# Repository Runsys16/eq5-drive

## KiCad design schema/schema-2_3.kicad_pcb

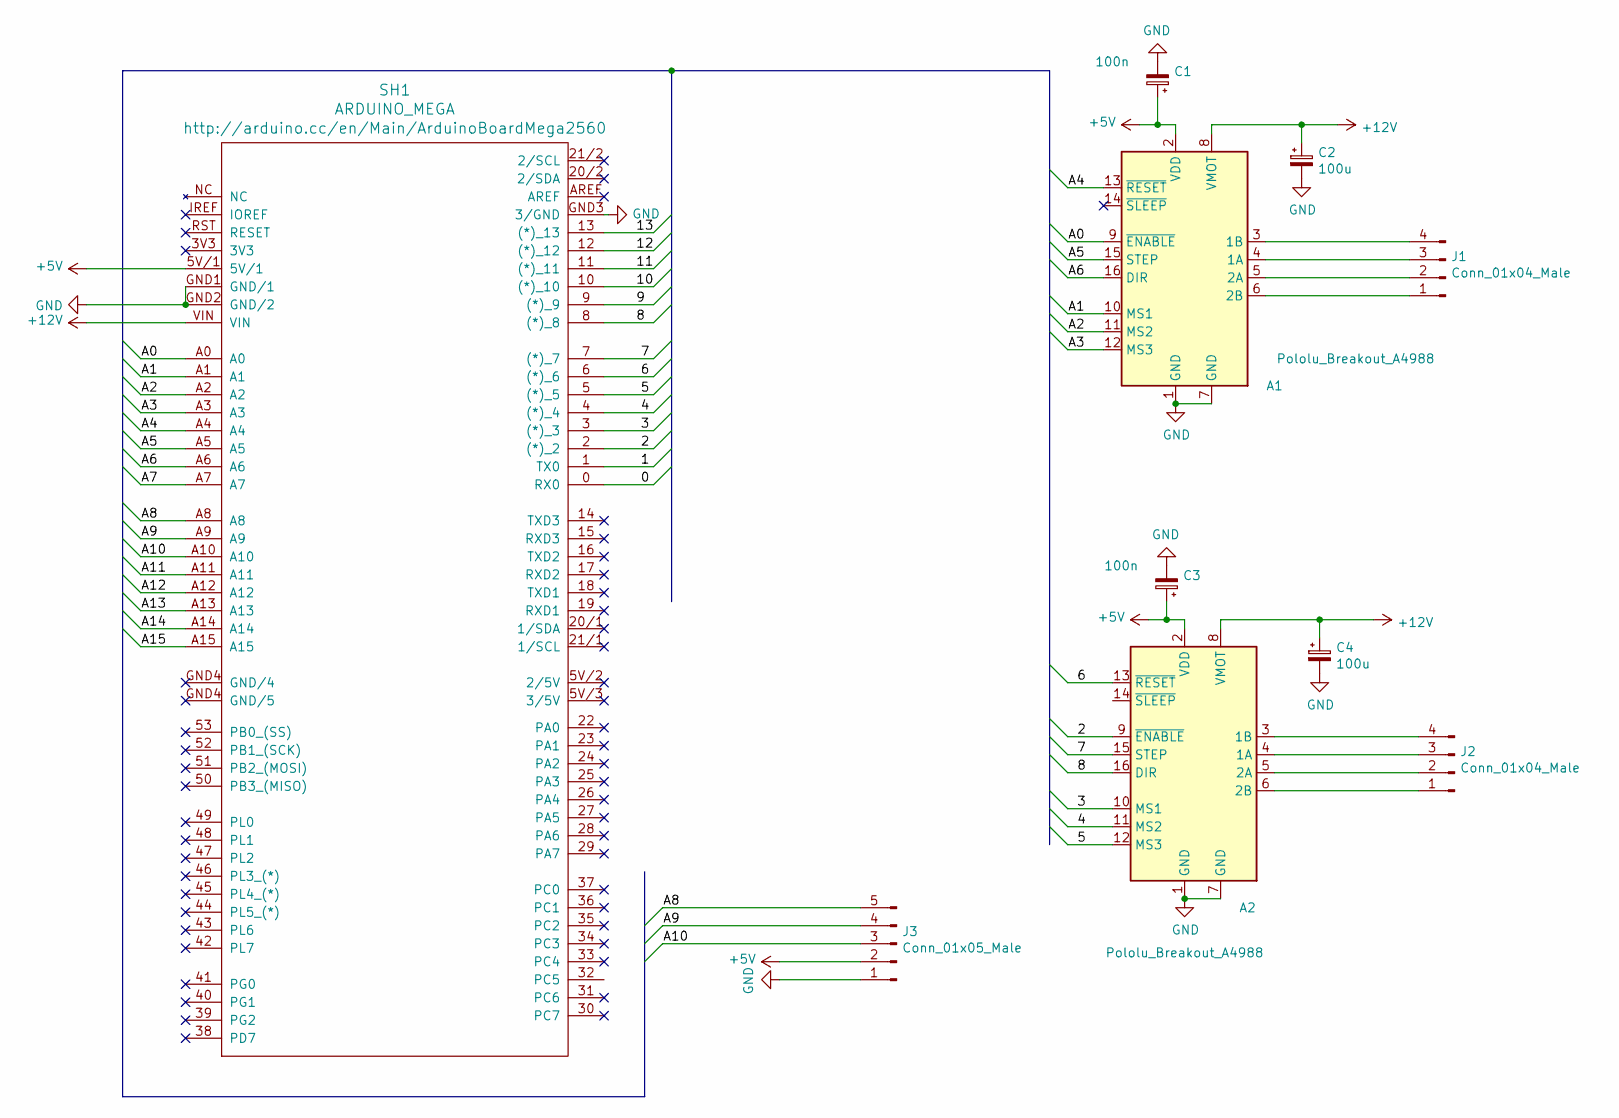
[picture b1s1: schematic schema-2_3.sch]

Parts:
A1, A2: Pololu_Breakout_A4988; Pololu_Breakout-16_15.2x20.3mm
C1, C3: 100n; C_Disc_D5.1mm_W3.2mm_P5.00mm
C2, C4: 100u; CP_Radial_D8.0mm_P5.00mm
J1, J2: Conn_01x04_Male; JST_XH_S4B-XH-A-1_1x04_P2.50mm_Horizontal
J3: Conn_01x05_Male; JST_XH_S5B-XH-A-1_1x05_P2.50mm_Horizontal
SH1: ARDUINO_MEGA; ARDUINO_MEGA_2560_R3_ELL

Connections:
+5V: A1.2 (VDD), A2.2 (VDD), C1.1, C3.1, J3.2, SH1.5V/1
+12V: A1.8 (VMOT), A2.8 (VMOT), C2.1, C4.1, SH1.VIN
/0: SH1.0 (RX0)
/1: SH1.1 (TX0)
/2: A2.9 (~ENABLE), SH1.2 ((*)_2)
/3: A2.10 (MS1), SH1.3 ((*)_3)
/4: A2.11 (MS2), SH1.4 ((*)_4)
/5: A2.12 (MS3), SH1.5 ((*)_5)
/6: A2.13 (~RESET), SH1.6 ((*)_6)
/7: A2.15 (STEP), SH1.7 ((*)_7)
/8: A2.16 (DIR), SH1.8 ((*)_8)
/9: SH1.9 ((*)_9)
/10: SH1.10 ((*)_10)
/11: SH1.11 ((*)_11)
/12: SH1.12 ((*)_12)
/13: SH1.13 ((*)_13)
/A0: A1.9 (~ENABLE), SH1.A0
/A1: A1.10 (MS1), SH1.A1
/A2: A1.11 (MS2), SH1.A2
/A3: A1.12 (MS3), SH1.A3
/A4: A1.13 (~RESET), SH1.A4
/A5: A1.15 (STEP), SH1.A5
/A6: A1.16 (DIR), SH1.A6
/A7: SH1.A7
/A8: J3.5, SH1.A8
/A9: J3.4, SH1.A9
/A10: J3.3, SH1.A10
/A11: SH1.A11
/A12: SH1.A12
/A13: SH1.A13
/A14: SH1.A14
/A15: SH1.A15
GND: A1.1 (GND), A1.7 (GND), A2.1 (GND), A2.7 (GND), C1.2, C2.2, C3.2, C4.2, J3.1, SH1.GND1 (GND/1), SH1.GND2 (GND/2), SH1.GND3 (3/GND)
unnamed: A1.3 (1B), J1.4
unnamed: A1.4 (1A), J1.3
unnamed: A1.5 (2A), J1.2
unnamed: A1.6 (2B), J1.1
unnamed: A2.3 (1B), J2.4
unnamed: A2.4 (1A), J2.3
unnamed: A2.5 (2A), J2.2
unnamed: A2.6 (2B), J2.1

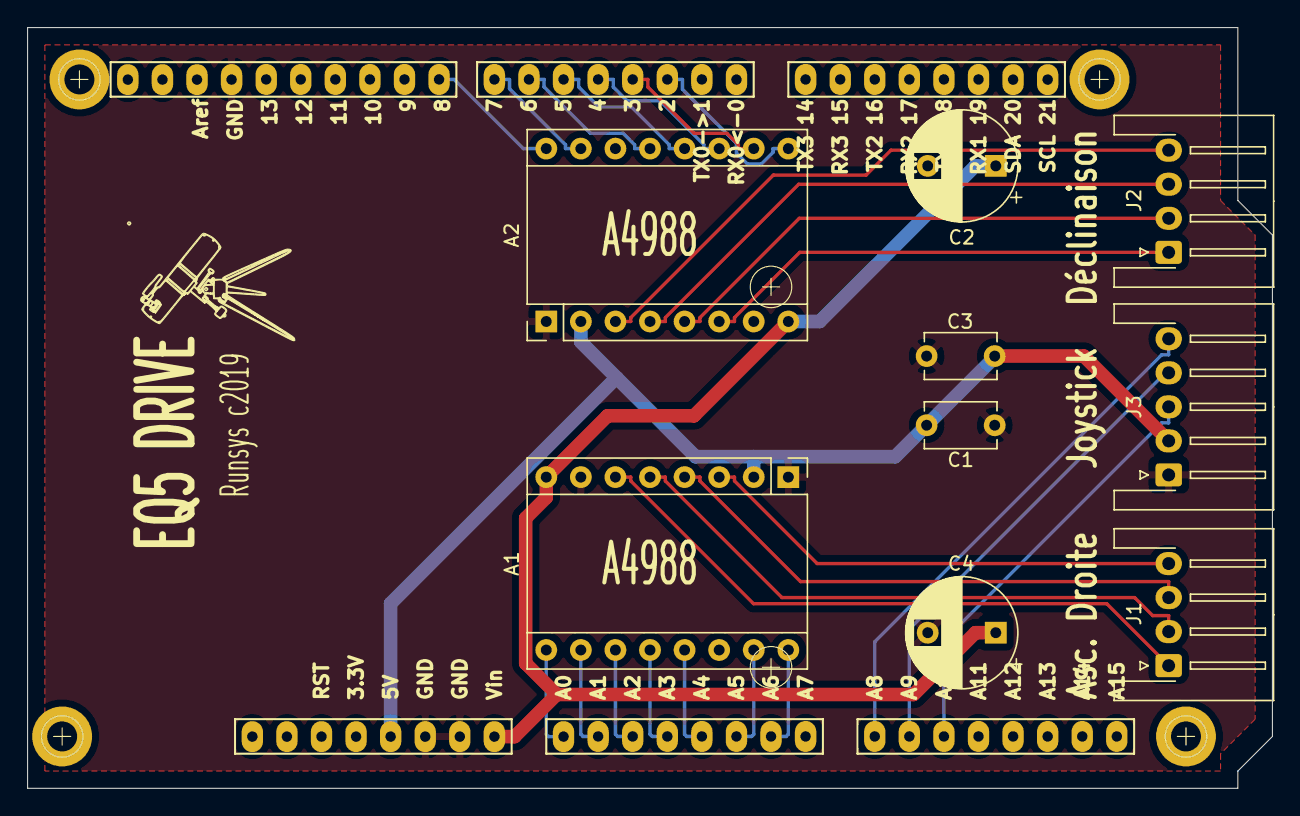
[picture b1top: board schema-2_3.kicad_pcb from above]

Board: 2 copper layers, 91.4 x 55.9 mm, 15 parts (0 on the bottom side), 28 nets.

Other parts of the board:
G0, G1: LOGO; tele
REF1, REF2, REF3: MountingHole_2.2mm_M2_Pad

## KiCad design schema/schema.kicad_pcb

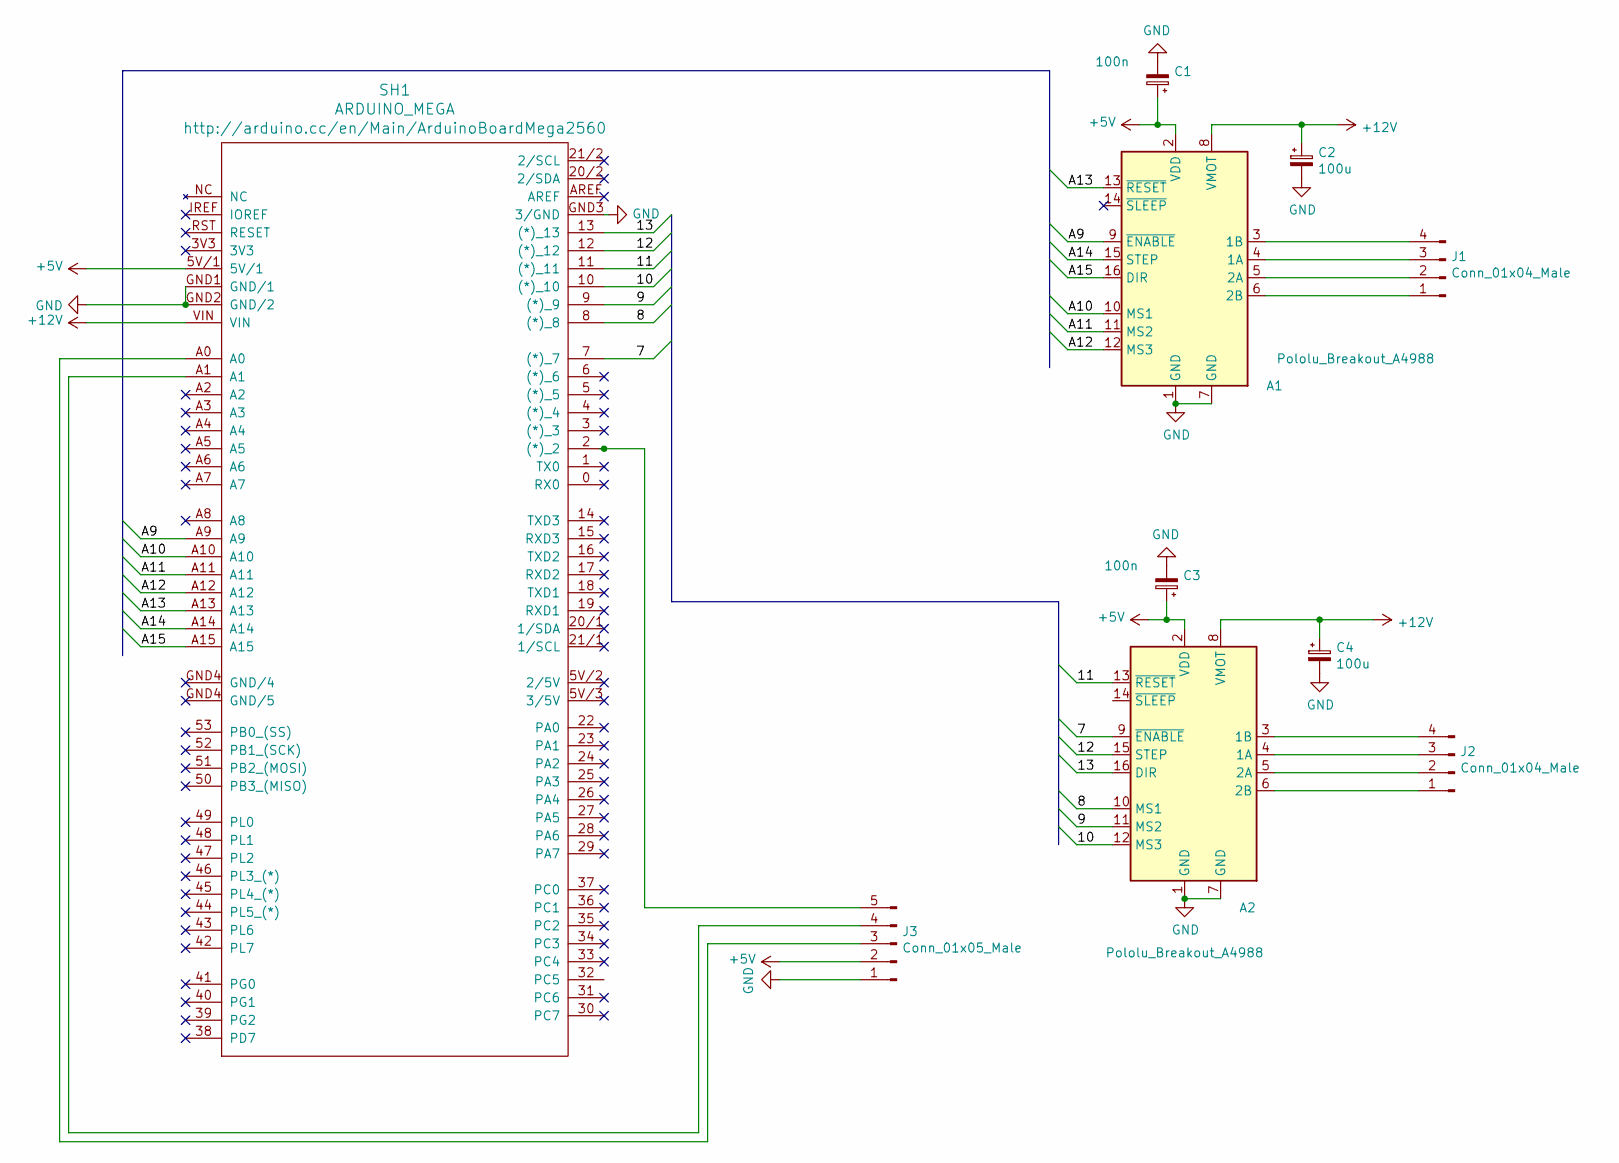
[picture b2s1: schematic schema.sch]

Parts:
A1, A2: Pololu_Breakout_A4988; Pololu_Breakout-16_15.2x20.3mm
C1, C3: 100n; C_Disc_D5.1mm_W3.2mm_P5.00mm
C2, C4: 100u; CP_Radial_D8.0mm_P5.00mm
J1, J2: Conn_01x04_Male; JST_XH_B4B-XH-A_1x04_P2.50mm_Vertical
J3: Conn_01x05_Male; JST_XH_B5B-XH-A_1x05_P2.50mm_Vertical
SH1: ARDUINO_MEGA; ARDUINO_MEGA_2560_R3_ELL

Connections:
+5V: A1.2 (VDD), A2.2 (VDD), C1.1, C3.1, J3.2, SH1.5V/1
+12V: A1.8 (VMOT), A2.8 (VMOT), C2.1, C4.1, SH1.VIN
/7: A2.9 (~ENABLE), SH1.7 ((*)_7)
/8: A2.10 (MS1), SH1.8 ((*)_8)
/9: A2.11 (MS2), SH1.9 ((*)_9)
/10: A2.12 (MS3), SH1.10 ((*)_10)
/11: A2.13 (~RESET), SH1.11 ((*)_11)
/12: A2.15 (STEP), SH1.12 ((*)_12)
/13: A2.16 (DIR), SH1.13 ((*)_13)
/A9: A1.9 (~ENABLE), SH1.A9
/A10: A1.10 (MS1), SH1.A10
/A11: A1.11 (MS2), SH1.A11
/A12: A1.12 (MS3), SH1.A12
/A13: A1.13 (~RESET), SH1.A13
/A14: A1.15 (STEP), SH1.A14
/A15: A1.16 (DIR), SH1.A15
GND: A1.1 (GND), A1.7 (GND), A2.1 (GND), A2.7 (GND), C1.2, C2.2, C3.2, C4.2, J3.1, SH1.GND1 (GND/1), SH1.GND2 (GND/2), SH1.GND3 (3/GND)
unnamed: A1.3 (1B), J1.4
unnamed: A1.4 (1A), J1.3
unnamed: A1.5 (2A), J1.2
unnamed: A1.6 (2B), J1.1
unnamed: A2.3 (1B), J2.4
unnamed: A2.4 (1A), J2.3
unnamed: A2.5 (2A), J2.2
unnamed: A2.6 (2B), J2.1
unnamed: J3.3, SH1.A0
unnamed: J3.4, SH1.A1
unnamed: J3.5, SH1.2 ((*)_2)

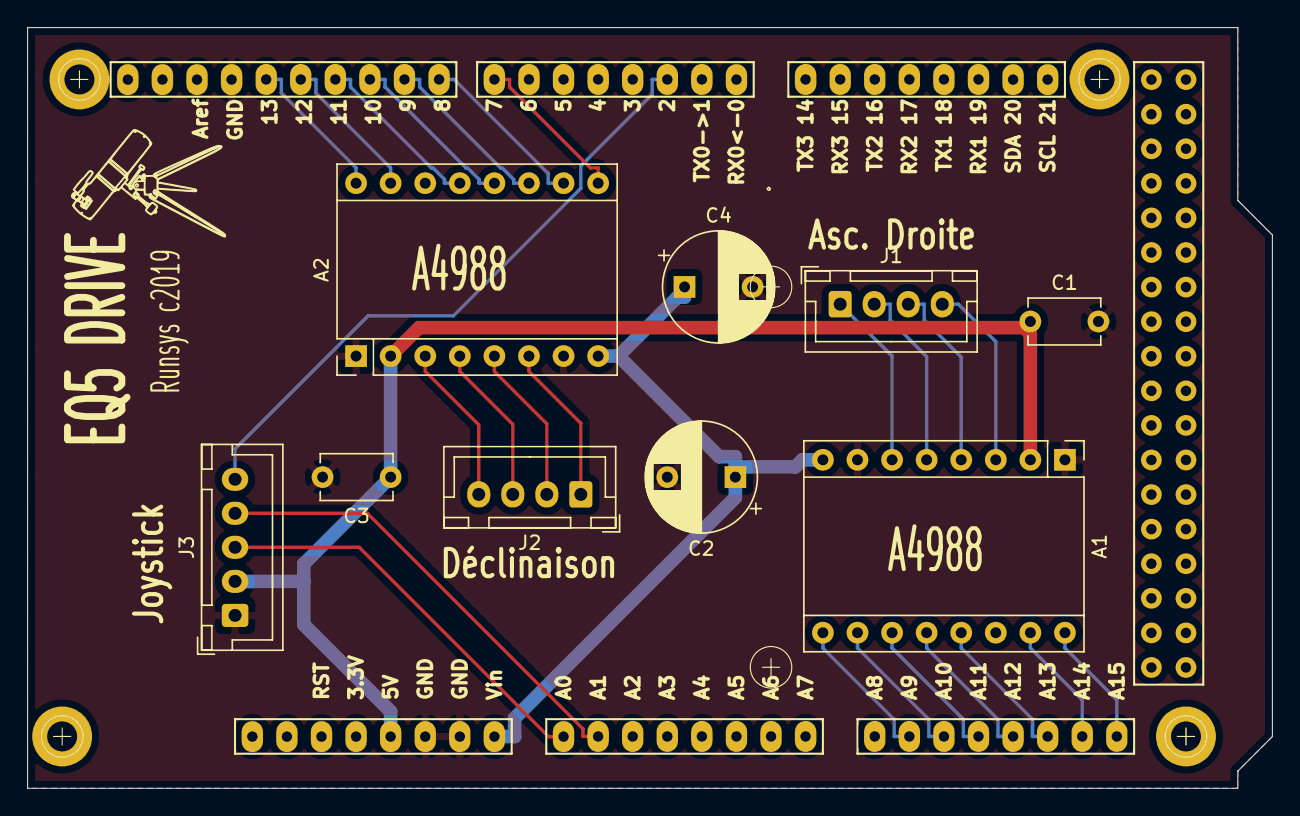
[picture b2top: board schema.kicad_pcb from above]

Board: 2 copper layers, 91.4 x 55.9 mm, 15 parts (0 on the bottom side), 28 nets.

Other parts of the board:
G0, G1: LOGO; tele
REF1, REF2, REF3: MountingHole_2.2mm_M2_Pad

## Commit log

2018-06-05 Init depot
2018-06-05 Ancienne version du suivi sideral ---------------------------------
2018-06-05 Nouvelle version du suivi sideral
2018-06-05 Suppression du joystick si une commande GOTO arrive
2018-06-06 Nouvelle fonction step() pour les drivers A4988. Nouveau parametre bool, pour savoir si l'on compte l'impulsion dans le compteur de driver
2018-06-24 Nouveau fichier de configuration de port Correction de bug La monture fait un deplacement trop court. Le compteur de pas se faisait aussibien sur les fronts montants que les fronts descendants Modifi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
2018-06-24 Probleme de compilation Suppression de 2 lignes de configurations bouton joystick (ancien fichier port.h)
2018-07-02 Ajout de la commande 'C' ------------------------ Le telescope tourne en spirale autour du point de visee courant. variable bCherche nbCherche uCherche
2018-08-09 Calcul du changement de vitesse Envoi de la position par defaut
2018-08-09 Rename eq-test en eq5-drive
2018-08-09 Ajout des valeurs mesuré pour le decalage, lors du suivi sideral
2018-08-15 Valeurs angulaire sous forme de constante
2018-08-19 Affichage du temps ecoule debut le branchement Modification du ratrappage du suivi siderale
2018-08-22 Ajout du double click sur la souris Cela change le sens de deplacement pour le joy. Le dernier axe utilise est inverse. Exemple on se deplace en ascension droite ... le dbl click modifie le sens de r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
2018-08-25 Modification de la gestion de la commande TODO commande souris a rendre compatible
2018-10-30 Prise en compte de la variable booleenne bSensSideral
2018-12-15 Modification de printInfo
2018-12-24 Modification de de la commande joystick
2018-12-24 Prise en compte du joystick ---------------------------- Fin de la modificaiton Nouvelle commande x et y ------------------------ Emulation de du joystick
2018-12-24 Gestion du double click
2018-12-28 Modfication de la commande joystick (suite) Ajout de la gestion LCD sur les ports 33,35,37,39,41,43 Aiifchage LCD correct par rapport à Stellarium
2018-12-29 FIX .f suppression de la compilation du LCD
2019-02-24 Ajout des commandes Mr et Ma Mr mode relatif Ma mode absolu
2019-03-01 Ajout des commande Mr et Ma
2019-03-02 Modification des la gestion absolu/relatif a,d en relatif A,D en absolu
2019-06-29 Modification du retour pour la commande 'g' iModification de la gestion du click de la souris
2019-12-22 Ajout du repertoire schema "kicad"
2019-12-26 Ajout des schemas
2019-12-26 Ajout de la librairie arduino Nouveau schema en vue du shield arduino mega
2019-12-27 Update PCB
2019-12-27 Deplacement des trous
2019-12-28 Suppression de la librairie
2019-12-28 Ajout du logo
2019-12-28 Ajout Logo telescope
2019-12-28 Modifiction du condo de 100nF
2019-12-29 Modificatin pour la 3D sur les connexteurs JST
2019-12-29 Changement de taille des pistes 12V et 5V
2019-12-30 2 version de projet kicad v1.0 v2.0
2019-12-30 Ajout des pins Arduinoshield dans le footprint pour l'affichage 3d de la carte
2019-12-31 Nouveau Footprint pour le driver A4988 Ajout du fichier 3D dans le pcb
2019-12-31 Export des fichiers gerber
2020-01-02 Nouvelle version Version : 1.0 2.0 2.2 2.3
2020-01-07 Changement des noms de version Ajout de la macro python freeroute.py
2020-04-02 Modification des schema
2020-04-05 AJOUT script de lancement de l'edition
2020-05-10 AJOUT Changement de l'affichage de compte rendu
2020-05-10 AJOUT CHangement du pas siderale
2020-05-10 AJOUT Gestion de l'exponenetielle sur le joystick Nouvelle COmmande exxx (-100 a 100 ) pourcentage d'exponentielle
2020-05-12 FIX le blocage du joystick <- rattrapage de jeu desactive Fignollage de l'exponentiel
2020-05-13 Changement de l'affichage des DEBUG
2020-05-13 AJOUT Notification lors du double click du joystick
2024-02-14 Deplacement a cheval sur 0h0m0s
2024-02-15 Envoi de la version du programme dans print_info Fix Ajout de qlq commentaires
2024-05-06 Modification du retour arduino
2024-05-28 Sauvegarde la config sur l'EEPROM Version 1.0.2
2024-05-31 Modification EEPROM
2024-06-14 Ajout de la doc
2024-06-14 Ajout de fichiers pdf pour la doc
2025-12-03 Version 1.0.4 Simulation du joystick pour la commande stellarium portable
2025-12-03 Gestion du joystick -------------------- Ajout du changement de sens sur appui du bouton lorsque le le joystick est au max, et qu el'on apuui sur le bouton, le joystick change de sens Dbl click chang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
2025-12-04 Suppression des echanges non indispensable
2026-03-26 Modification du script ed
